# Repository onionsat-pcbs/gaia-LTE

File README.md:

# Gaia LTE
LTE PBC for OnionSAT Gaia satellite.

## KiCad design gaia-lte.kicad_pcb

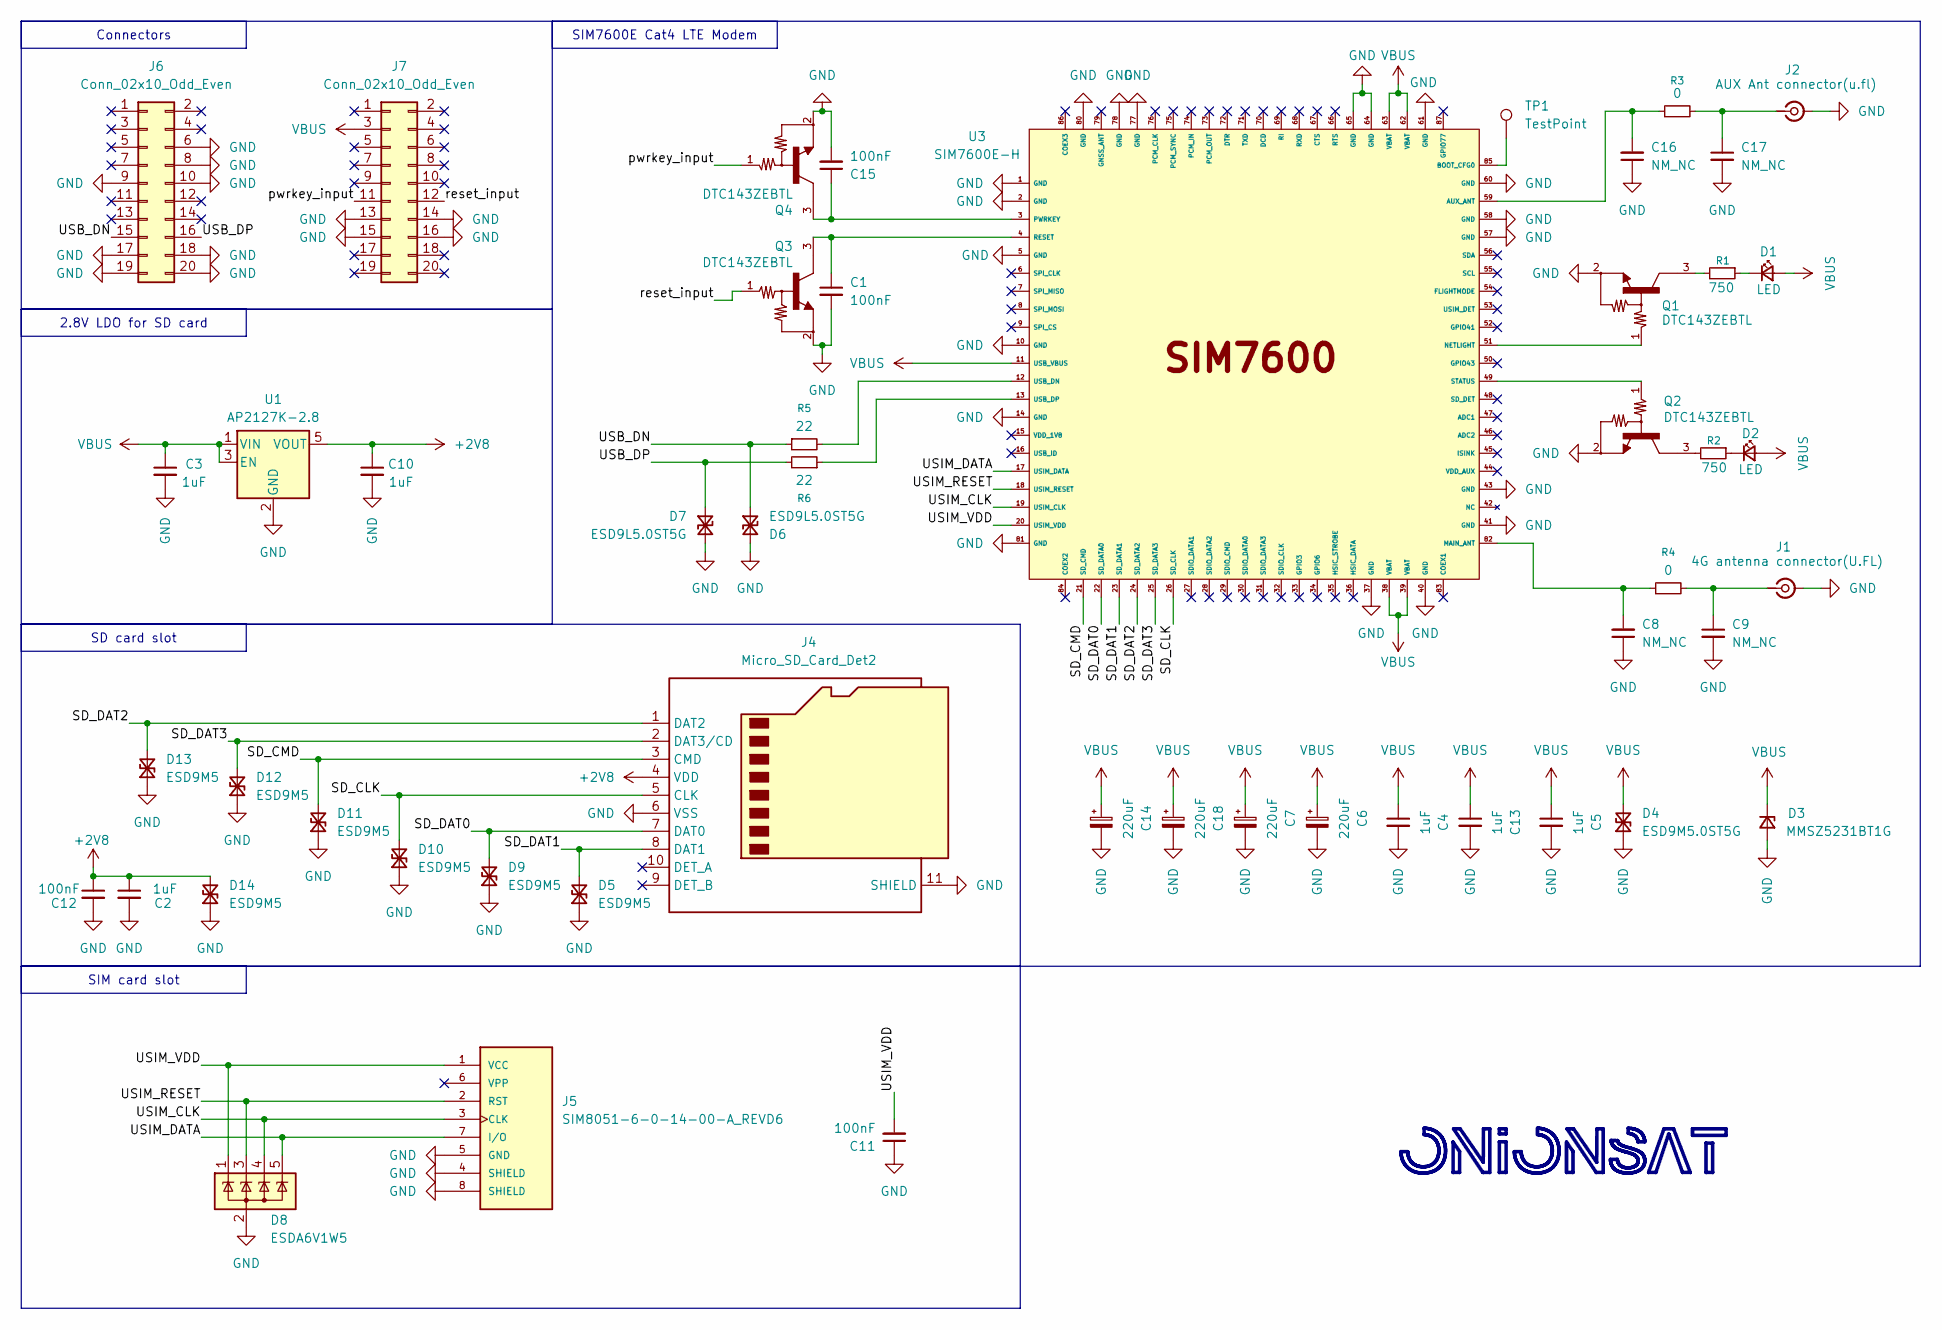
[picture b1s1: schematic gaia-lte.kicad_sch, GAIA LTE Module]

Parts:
C1, C11, C15: 100nF; C_0603_1608Metric
C2: 1uF; C_0603_1608Metric
C3, C10, C13: 1uF; C_0402_1005Metric
C4, C5: 1uF; C_1812_4532Metric
C6, C7, C14, C18: 220uF; CP_Elec_5x5.9
C8, C9, C16, C17: NM_NC; C_0402_1005Metric
C12: 100nF; C_0402_1005Metric
D1, D2: LED; LED_0402_1005Metric
D3: MMSZ5231BT1G; D_SOD-123
D4: ESD9M5.0ST5G; D_SOD-923
D5, D9, D10, D11, D12, D13, D14: ESD9M5; D_SOD-923
D6, D7: ESD9L5.0ST5G; D_SOD-923
D8: ESDA6V1W5; SOT-23-5
J1: 4G antenna connector(U.FL); U.FL_Hirose_U.FL-R-SMT-1_Vertical
J2: AUX Ant connector(u.fl); U.FL_Hirose_U.FL-R-SMT-1_Vertical
J4: Micro_SD_Card_Det2; microSD_HC_Hirose_DM3D-SF
J5: SIM8051-6-0-14-00-A_REVD6; GCT_SIM8051-6-0-14-00-A_REVD6; PARTREV D6
J6, J7: Conn_02x10_Odd_Even; Gaia_connector_2_4layer
Q1, Q2, Q3, Q4: DTC143ZEBTL; PARTREV 004
R1, R2: 750; R_0402_1005Metric
R3, R4: 0; R_0402_1005Metric
R5, R6: 22; R_0402_1005Metric
TP1: TestPoint; TestPoint_Pad_1.5x1.5mm
U1: AP2127K-2.8; SOT-23-5
U3: SIM7600E-H; SIM7600

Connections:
+2V8: C2.1, C10.1, C12.1, D14.2 (A2), J4.4 (VDD), U1.5 (VOUT)
/SD_CLK: D10.2 (A2), J4.5 (CLK), U3.26 (SD_CLK)
/SD_CMD: D11.2 (A2), J4.3 (CMD), U3.21 (SD_CMD)
/SD_DAT0: D9.2 (A2), J4.7 (DAT0), U3.22 (SD_DATA0)
/SD_DAT1: D5.2 (A2), J4.8 (DAT1), U3.23 (SD_DATA1)
/SD_DAT2: D13.2 (A2), J4.1 (DAT2), U3.24 (SD_DATA2)
/SD_DAT3: D12.2 (A2), J4.2 (DAT3/CD), U3.25 (SD_DATA3)
/USB_DN: D6.1 (A1), J6.15, R5.1
/USB_DP: D7.1 (A1), J6.16, R6.2
/USIM_CLK: D8.4 (K), J5.3 (CLK), U3.19 (USIM_CLK)
/USIM_DATA: D8.5 (K), J5.7 (I/O), U3.17 (USIM_DATA)
/USIM_RESET: D8.3 (K), J5.2 (RST), U3.18 (USIM_RESET)
/USIM_VDD: C11.2, D8.1 (K), J5.1 (VCC), U3.20 (USIM_VDD)
/pwrkey_input: J7.11, Q4.1
/reset_input: J7.12, Q3.1
GND: C1.2, C2.2, C3.2, C4.2, C5.2, C6.2, C7.2, C8.1, C9.2, C10.2, C11.1, C12.2, C13.2, C14.2, C15.2, C16.1, C17.2, C18.2, D3.2 (A), D4.1 (A1), D5.1 (A1), D6.2 (A2), D7.2 (A2), D8.2 (A), D9.1 (A1), D10.1 (A1), D11.1 (A1), D12.1 (A1), D13.1 (A1), D14.1 (A1), J1.2 (Ext), J2.2 (Ext), J4.6 (VSS), J4.11 (SHIELD), J5.4 (SHIELD), J5.5 (GND), J5.8 (SHIELD), J6.6, J6.8, J6.9, J6.10, J6.17, J6.18, J6.19, J6.20, J7.13, J7.14, J7.15, J7.16, Q1.2, Q2.2, Q3.2, Q4.2, U1.2 (GND), U3.1 (GND), U3.2 (GND), U3.5 (GND), U3.10 (GND), U3.14 (GND), U3.37 (GND), U3.40 (GND), U3.41 (GND), U3.43 (GND), U3.57 (GND), U3.58 (GND), U3.60 (GND), U3.61 (GND), U3.64 (GND), U3.65 (GND), U3.77 (GND), U3.78 (GND), U3.80 (GND), U3.81 (GND)
unnamed: D1.1 (K), R1.1
unnamed: D2.1 (K), R2.1
unnamed: C9.1, J1.1 (In), R4.2
unnamed: C17.1, J2.1 (In), R3.2
unnamed: Q1.3, R1.2
unnamed: Q2.3, R2.2
unnamed: C16.2, R3.1, U3.59 (AUX_ANT)
unnamed: TP1.1, U3.85 (BOOT_CFG0)
unnamed: C8.2, R4.1, U3.82 (MAIN_ANT)
unnamed: Q1.1, U3.51 (NETLIGHT)
unnamed: C15.1, Q4.3, U3.3 (PWRKEY)
unnamed: C1.1, Q3.3, U3.4 (RESET)
unnamed: Q2.1, U3.49 (STATUS)
unnamed: R5.2, U3.12 (USB_DN)
unnamed: R6.1, U3.13 (USB_DP)
VBUS: C3.1, C4.1, C5.1, C6.1, C7.1, C13.1, C14.1, C18.1, D1.2 (A), D2.2 (A), D3.1 (K), D4.2 (A2), J7.3, U1.1 (VIN), U1.3 (EN), U3.11 (USB_VBUS), U3.38 (VBAT), U3.39 (VBAT), U3.62 (VBAT), U3.63 (VBAT)

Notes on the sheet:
SD card slot
SIM card slot
Connectors
2.8V LDO for SD card
SIM7600E Cat4 LTE Modem

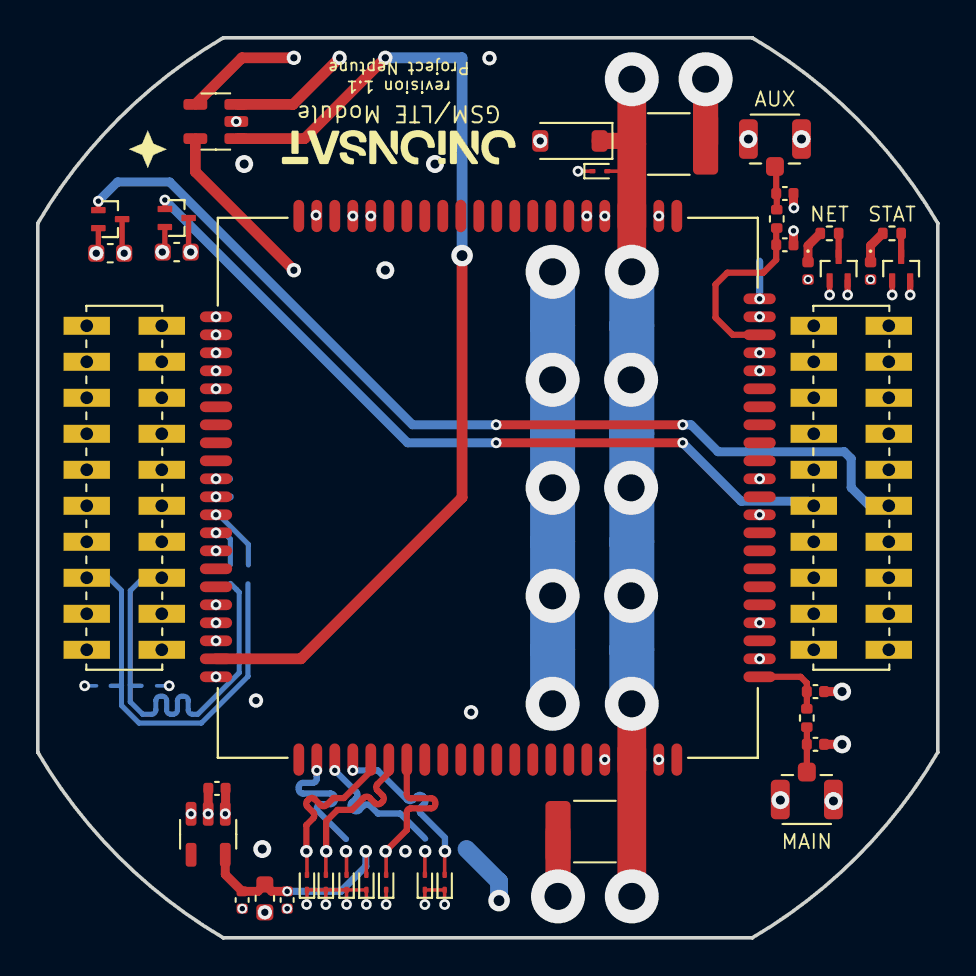
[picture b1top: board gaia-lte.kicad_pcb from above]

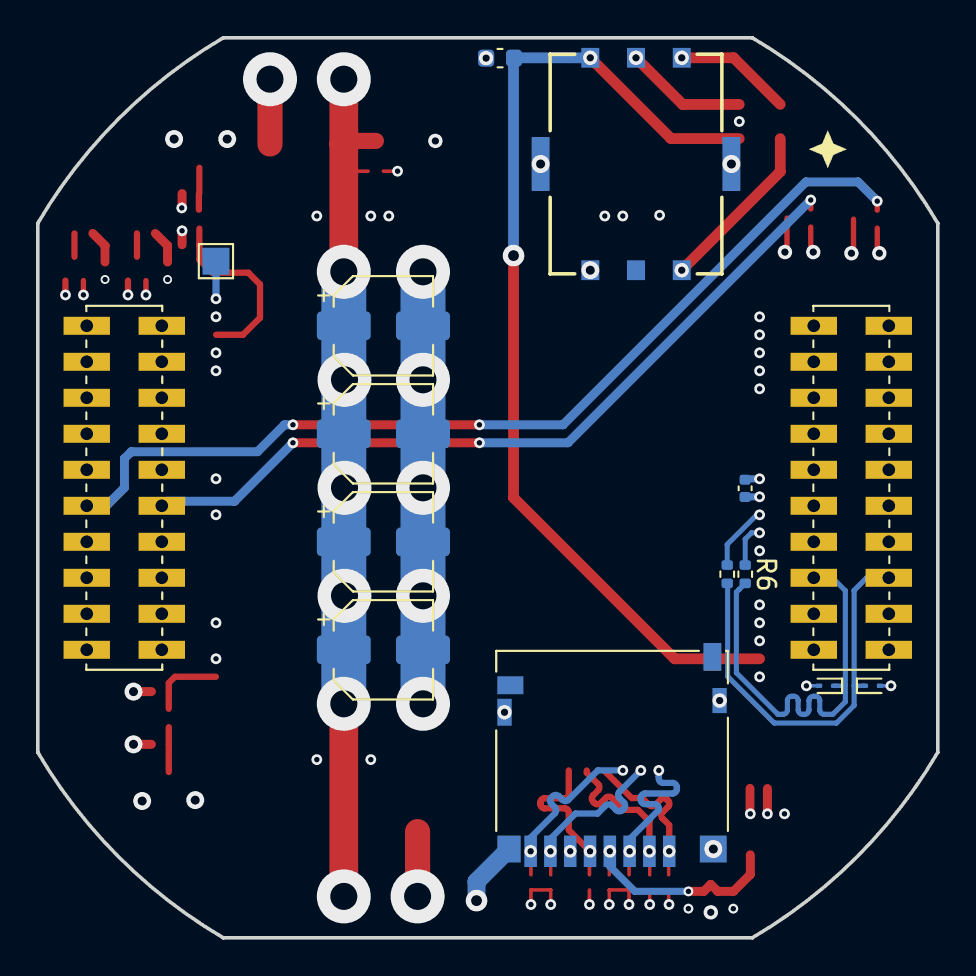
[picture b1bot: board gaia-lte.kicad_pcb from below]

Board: 6 copper layers, 50.0 x 50.0 mm, 51 parts (13 on the bottom side), 32 nets.

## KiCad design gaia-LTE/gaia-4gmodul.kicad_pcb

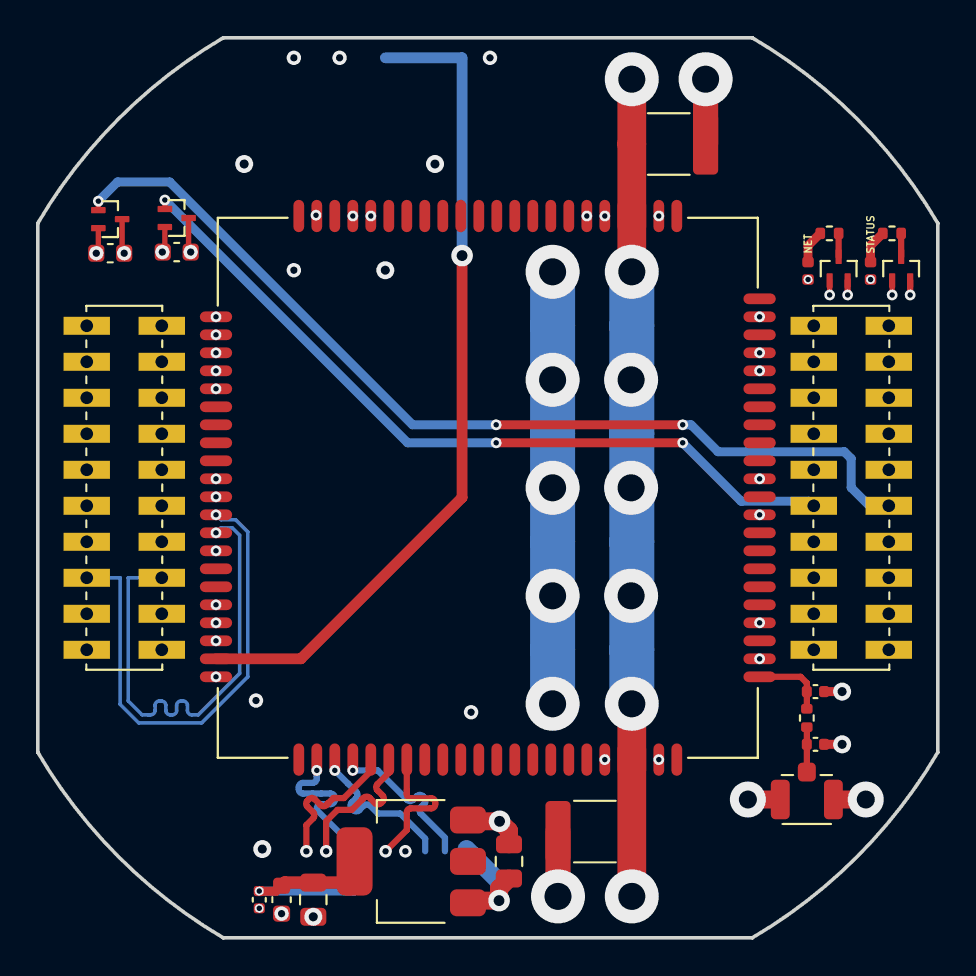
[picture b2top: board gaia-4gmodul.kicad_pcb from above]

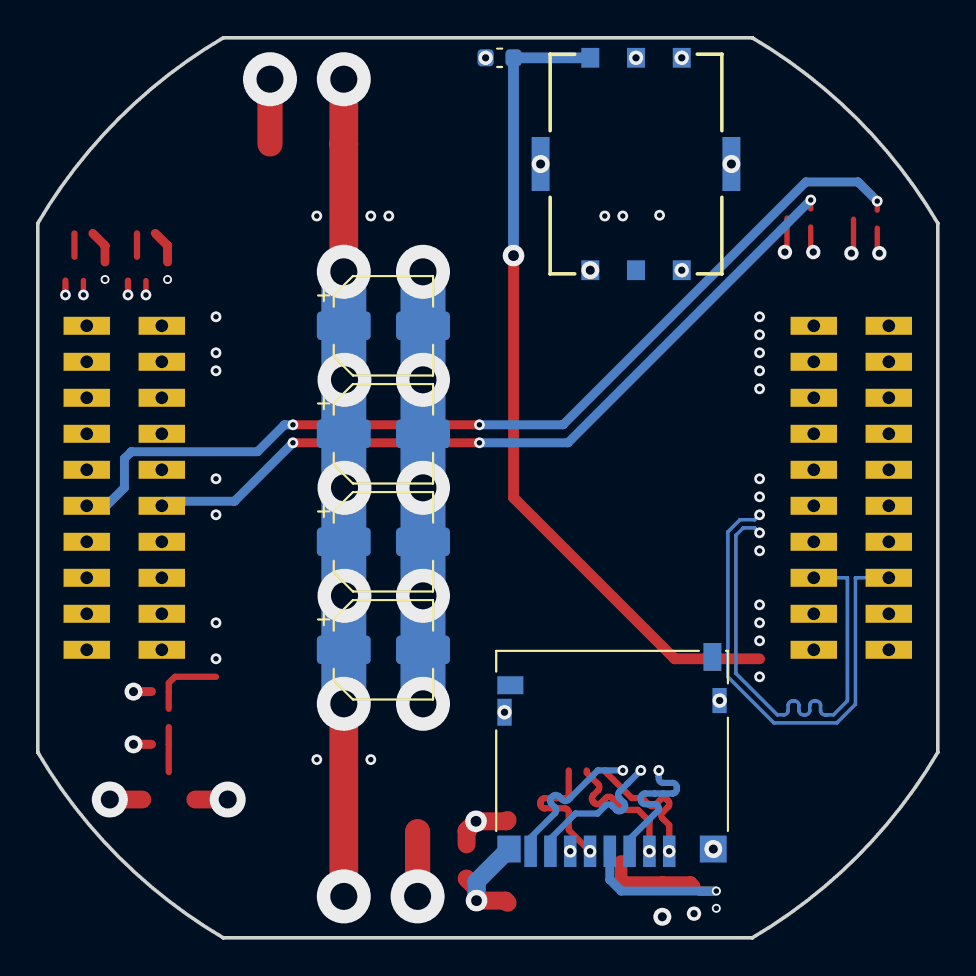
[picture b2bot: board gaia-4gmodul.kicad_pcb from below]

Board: 6 copper layers, 50.0 x 50.0 mm, 31 parts (7 on the bottom side), 27 nets.

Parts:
C1, C10, C15: 100nF; C_0603_1608Metric
C2, C3, C6, C7: 220uF; CP_Elec_5x5.9
C4, C5: 1uF; C_1812_4532Metric
C8, C9: NM_NC; C_0402_1005Metric
C11: 4.7uF; C_0603_1608Metric
C12: 100nF; C_0402_1005Metric
C13, C14: 1uF; C_0805_2012Metric
D1, D2: LED; LED_0402_1005Metric
J1: 4G antenna connector(U.FL); U.FL_Hirose_U.FL-R-SMT-1_Vertical
J3: Micro_SD_Card_Det2; microSD_HC_Hirose_DM3D-SF
J4: SIM8051-6-0-14-00-A_REVD6; GCT_SIM8051-6-0-14-00-A_REVD6
Q1, Q2, Q3, Q4: DTC143ZEBTL
R1, R2: 750; R_0402_1005Metric
R4: 0; R_0402_1005Metric
U1: Gaia Connector A; Gaia_connector_2_4layer
U2: Gaia Connector B; Gaia_connector_2_4layer
U3: SIM7600E-H; SIM7600
U4: ADP3338AKCZ-2.85R7

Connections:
/SD_CLK: J3.5 (CLK), U3.26 (SD_CLK)
/SD_CMD: J3.3 (CMD), U3.21 (SD_CMD)
/SD_DAT0: J3.7 (DAT0), U3.22 (SD_DATA0)
/SD_DAT1: J3.8 (DAT1), U3.23 (SD_DATA1)
/SD_DAT2: J3.1 (DAT2), U3.24 (SD_DATA2)
/SD_DAT3: J3.2 (DAT3/CD), U3.25 (SD_DATA3)
/USB_DN: U2.15 (4G_USB_DN), U3.12 (USB_DN)
/USB_DP: U2.16 (4G_USB_DP), U3.13 (USB_DP)
/USIM_CLK: J4.3 (CLK), U3.19 (USIM_CLK)
/USIM_DATA: J4.7 (I/O), U3.17 (USIM_DATA)
/USIM_RESET: J4.2 (RST), U3.18 (USIM_RESET)
/USIM_VDD: C10.2, J4.1 (VCC), U3.20 (USIM_VDD)
/netlight: Q1.1, U3.51 (NETLIGHT)
/pwrkey: C15.1, Q4.3, U3.3 (PWRKEY)
/pwrkey_input: Q4.1, U1.11 (NC)
/reset: C1.1, Q3.3, U3.4 (RESET)
/reset_input: Q3.1, U1.12 (NC)
/sdCard/SD_2.85V: C11.1, C12.1, C13.1, J3.4 (VDD), U4.4 (Vout)
/status: Q2.1, U3.49 (STATUS)
GND: C1.2, C2.2, C3.2, C4.2, C5.2, C6.2, C7.2, C8.1, C9.2, C10.1, C11.2, C12.2, C13.2, C14.1, C15.2, J1.2 (Ext), J3.6 (VSS), J3.11 (SHIELD), J4.4 (SHIELD), J4.5 (GND), J4.8 (SHIELD), Q1.2, Q2.2, Q3.2, Q4.2, U1.13 (Ground), U1.14 (Ground), U1.15 (Ground), U1.16 (Ground), U2.8 (Ground), U2.10 (Ground), U2.17 (Ground), U2.18 (Ground), U2.19 (Ground), U2.20 (Ground), U3.1 (GND), U3.2 (GND), U3.5 (GND), U3.10 (GND), U3.14 (GND), U3.37 (GND), U3.40 (GND), U3.41 (GND), U3.43 (GND), U3.57 (GND), U3.58 (GND), U3.60 (GND), U3.61 (GND), U3.64 (GND), U3.65 (GND), U3.77 (GND), U3.78 (GND), U3.80 (GND), U3.81 (GND), U4.1 (GND)
unnamed: D1.1 (K), R1.1
unnamed: D2.1 (K), R2.1
unnamed: C9.1, J1.1 (In), R4.2
unnamed: Q1.3, R1.2
unnamed: Q2.3, R2.2
unnamed: C8.2, R4.1, U3.82 (MAIN_ANT)
Vbat: C2.1, C3.1, C4.1, C5.1, C6.1, C7.1, C14.2, D1.2 (A), D2.2 (A), U1.3 (VOUT_A2), U3.11 (USB_VBUS), U3.38 (VBAT), U3.39 (VBAT), U3.62 (VBAT), U3.63 (VBAT), U4.3 (Vin)

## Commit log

2025-08-28 initial relase
2025-08-30 ready
2025-08-30 USB fix
2025-09-16 preparing to install TVS
2025-09-17 adding TVS diodes 1/2
2025-09-17 schematic arragements
2025-09-17 naming&location fixes
2025-09-17 ready for production
2025-09-18 adding direction arrow
2025-09-18 adding star as orientation + creating schema pdf
2025-09-18 adding silkscreen to bottoms
2025-09-18 creating production files
2026-01-03 3d models
2026-01-07 fixing 3d models
2026-01-26 header fix
2026-02-01 v1.1 - PROD
